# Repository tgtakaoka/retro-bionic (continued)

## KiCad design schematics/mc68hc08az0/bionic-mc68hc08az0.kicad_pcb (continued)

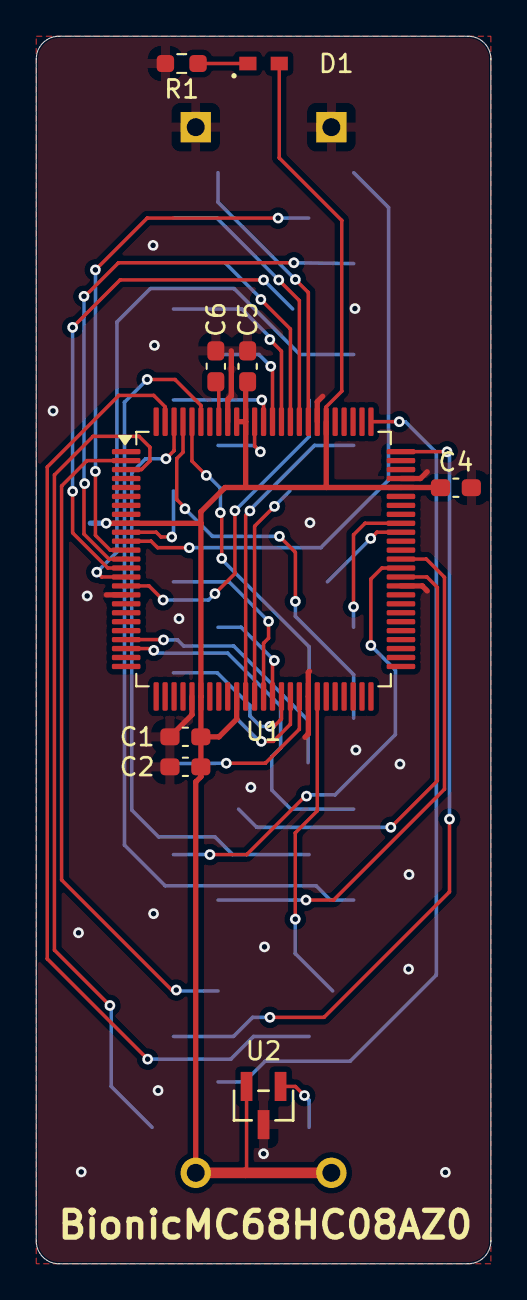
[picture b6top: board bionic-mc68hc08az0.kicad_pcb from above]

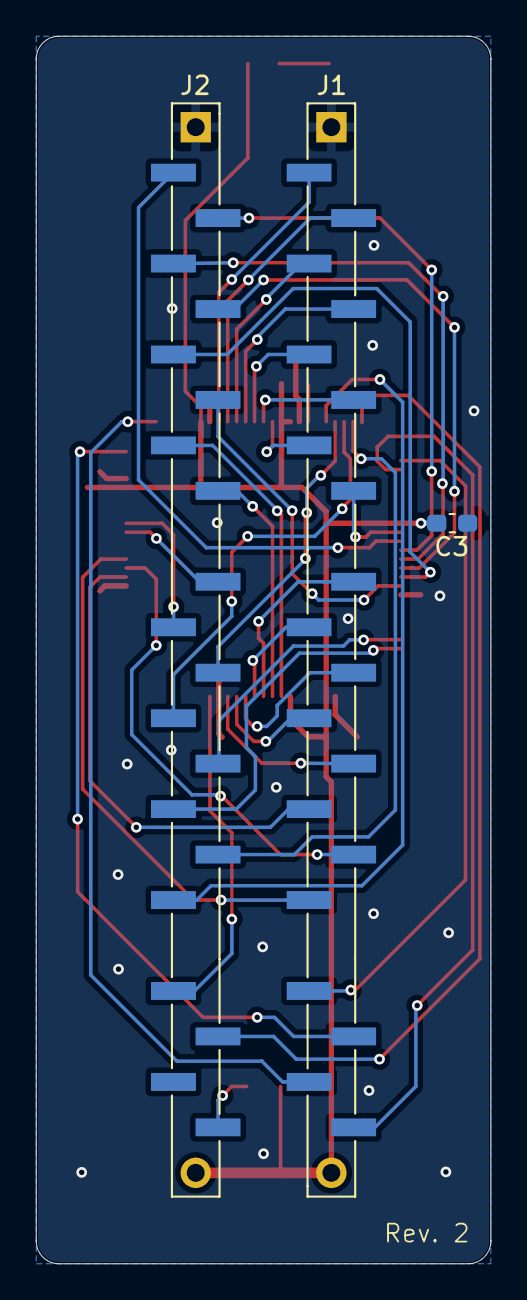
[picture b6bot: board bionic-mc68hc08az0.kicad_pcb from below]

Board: 2 copper layers, 25.4 x 68.6 mm, 12 parts (3 on the bottom side), 43 nets.

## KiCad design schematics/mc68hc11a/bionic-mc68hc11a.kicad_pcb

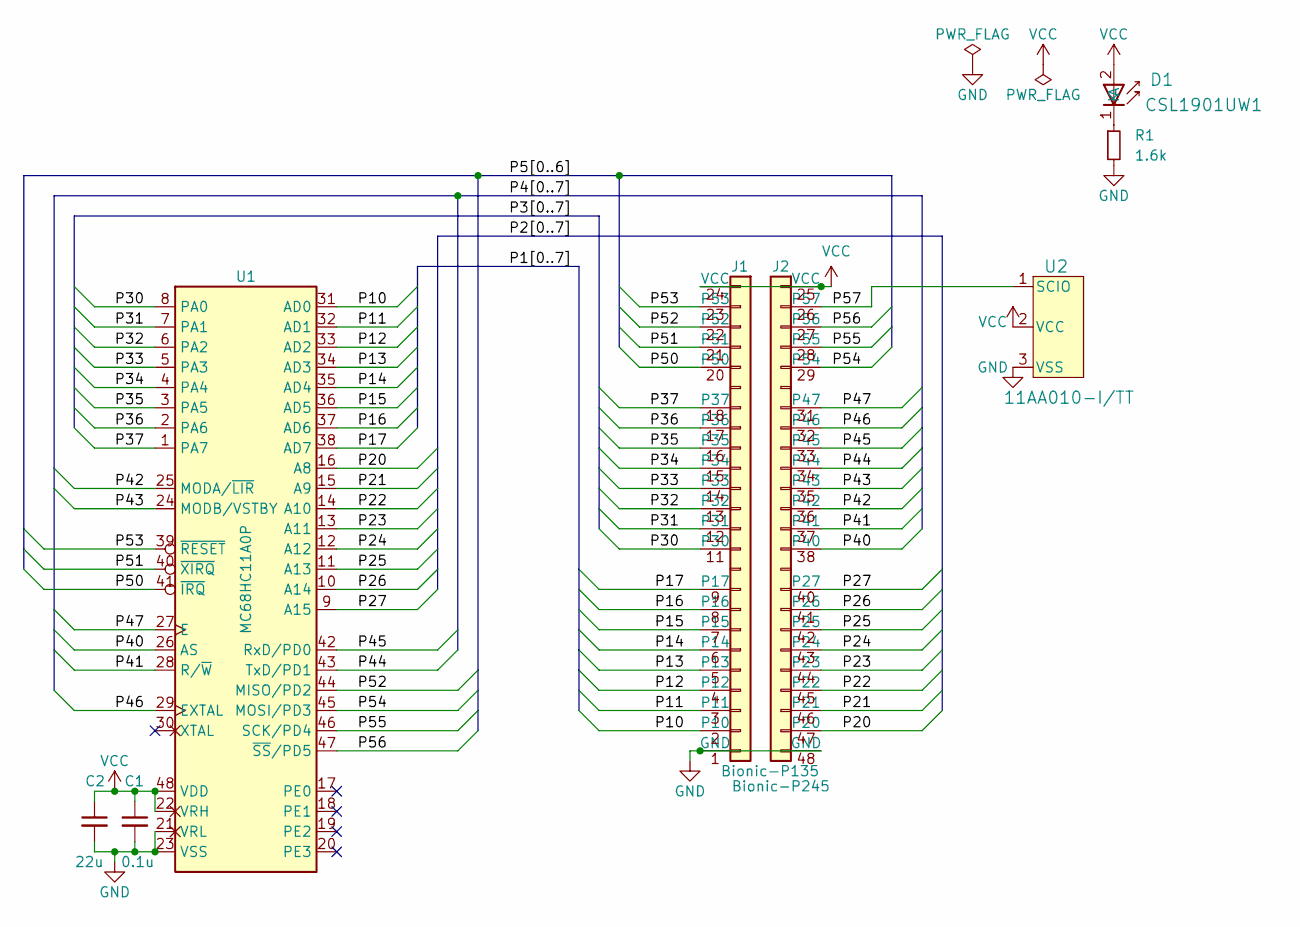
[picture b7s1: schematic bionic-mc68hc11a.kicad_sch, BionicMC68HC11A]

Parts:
C1: 0.1u; C_0603_1608Metric_Pad1.08x0.95mm_HandSolder
C2: 22u; C_0603_1608Metric_Pad1.08x0.95mm_HandSolder
D1: CSL1901UW1; LED_CSL1901UW1_ROM-M
J1: Bionic-P135; Bionic-P135_THT
J2: Bionic-P245; Bionic-P245_THT
R1: 1.6k; R_0603_1608Metric_Pad0.98x0.95mm_HandSolder
U1: MC68HC11A0P; DIP-48_W15.24mm_Socket
U2: 11AA010-I/TT; SOT-23_MC_MCH-M

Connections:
/P10: J1.2 (P10), U1.31 (AD0)
/P11: J1.3 (P11), U1.32 (AD1)
/P12: J1.4 (P12), U1.33 (AD2)
/P13: J1.5 (P13), U1.34 (AD3)
/P14: J1.6 (P14), U1.35 (AD4)
/P15: J1.7 (P15), U1.36 (AD5)
/P16: J1.8 (P16), U1.37 (AD6)
/P17: J1.9 (P17), U1.38 (AD7)
/P20: J2.47 (P20), U1.16 (A8)
/P21: J2.46 (P21), U1.15 (A9)
/P22: J2.45 (P22), U1.14 (A10)
/P23: J2.44 (P23), U1.13 (A11)
/P24: J2.43 (P24), U1.12 (A12)
/P25: J2.42 (P25), U1.11 (A13)
/P26: J2.41 (P26), U1.10 (A14)
/P27: J2.40 (P27), U1.9 (A15)
/P30: J1.11 (P30), U1.8 (PA0)
/P31: J1.12 (P31), U1.7 (PA1)
/P32: J1.13 (P32), U1.6 (PA2)
/P33: J1.14 (P33), U1.5 (PA3)
/P34: J1.15 (P34), U1.4 (PA4)
/P35: J1.16 (P35), U1.3 (PA5)
/P36: J1.17 (P36), U1.2 (PA6)
/P37: J1.18 (P37), U1.1 (PA7)
/P40: J2.38 (P40), U1.26 (AS)
/P41: J2.37 (P41), U1.28 (R/~W)
/P42: J2.36 (P42), U1.25 (MODA/~LIR)
/P43: J2.35 (P43), U1.24 (MODB/VSTBY)
/P44: J2.34 (P44), U1.43 (TxD/PD1)
/P45: J2.33 (P45), U1.42 (RxD/PD0)
/P46: J2.32 (P46), U1.29 (EXTAL)
/P47: J2.31 (P47), U1.27 (E)
/P50: J1.20 (P50), U1.41 (~IRQ)
/P51: J1.21 (P51), U1.40 (~XIRQ)
/P52: J1.22 (P52), U1.44 (MISO/PD2)
/P53: J1.23 (P53), U1.39 (~RESET)
/P54: J2.29 (P54), U1.45 (MOSI/PD3)
/P55: J2.28 (P55), U1.46 (SCK/PD4)
/P56: J2.27 (P56), U1.47 (~SS/PD5)
/P57: J2.26 (P57), U2.1 (SCIO)
GND: C1.2, C2.2, J1.1 (GND), J2.48 (GND), R1.2, U1.21 (VRL), U1.23 (VSS), U2.3 (VSS)
unnamed: D1.1 (K), R1.1
VCC: C1.1, C2.1, D1.2 (A), J1.24 (VCC), J2.25 (VCC), U1.22 (VRH), U1.48 (VDD), U2.2 (VCC)

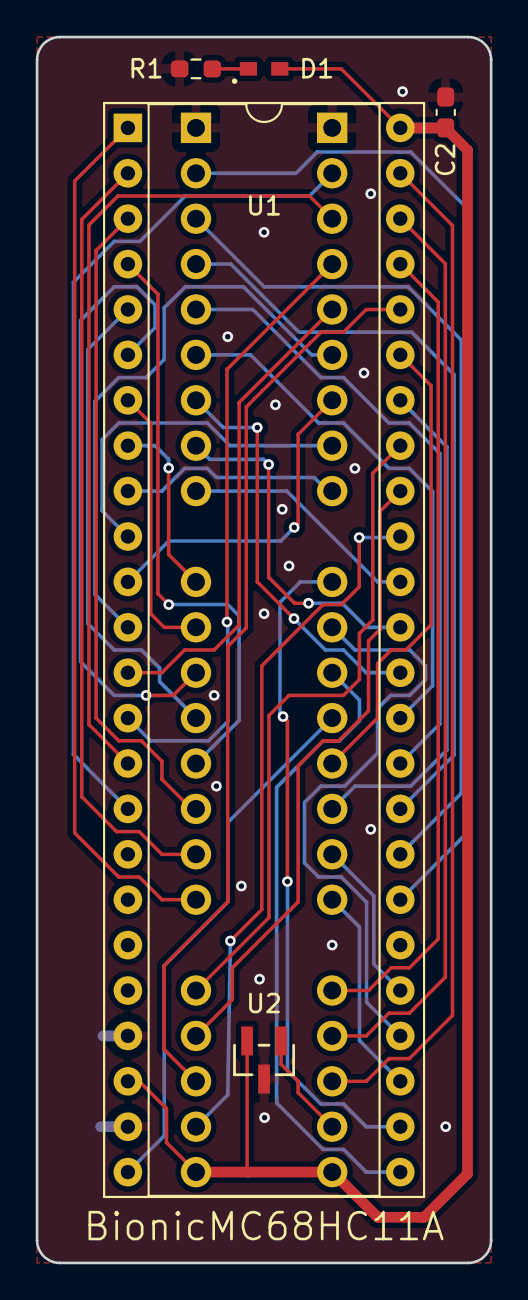
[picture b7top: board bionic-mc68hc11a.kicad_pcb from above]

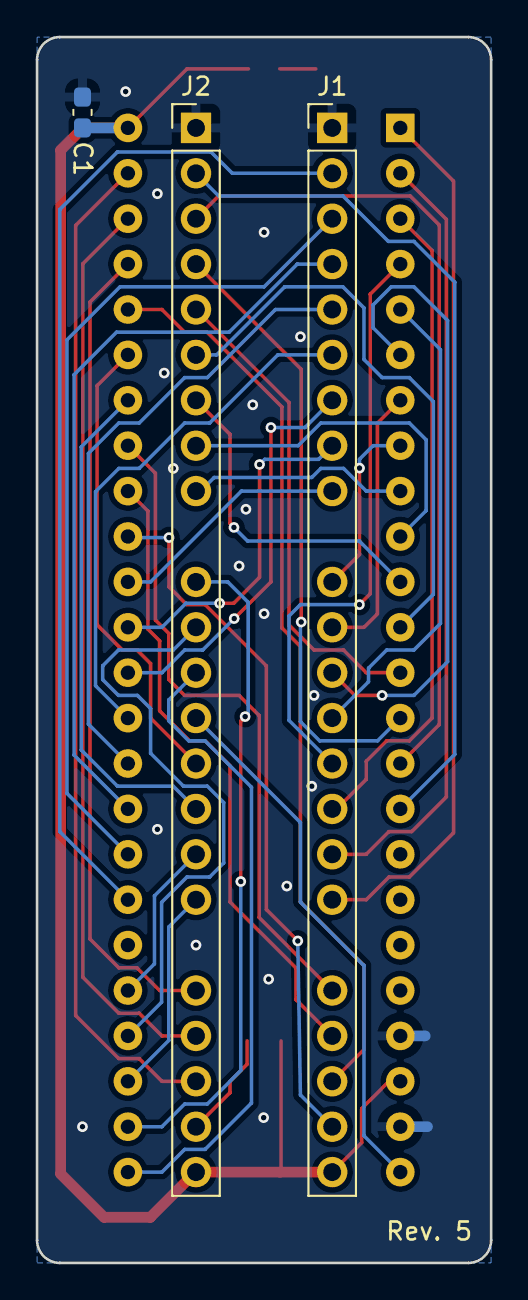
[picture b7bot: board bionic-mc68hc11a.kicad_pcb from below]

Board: 2 copper layers, 25.4 x 68.6 mm, 8 parts (3 on the bottom side), 43 nets.
